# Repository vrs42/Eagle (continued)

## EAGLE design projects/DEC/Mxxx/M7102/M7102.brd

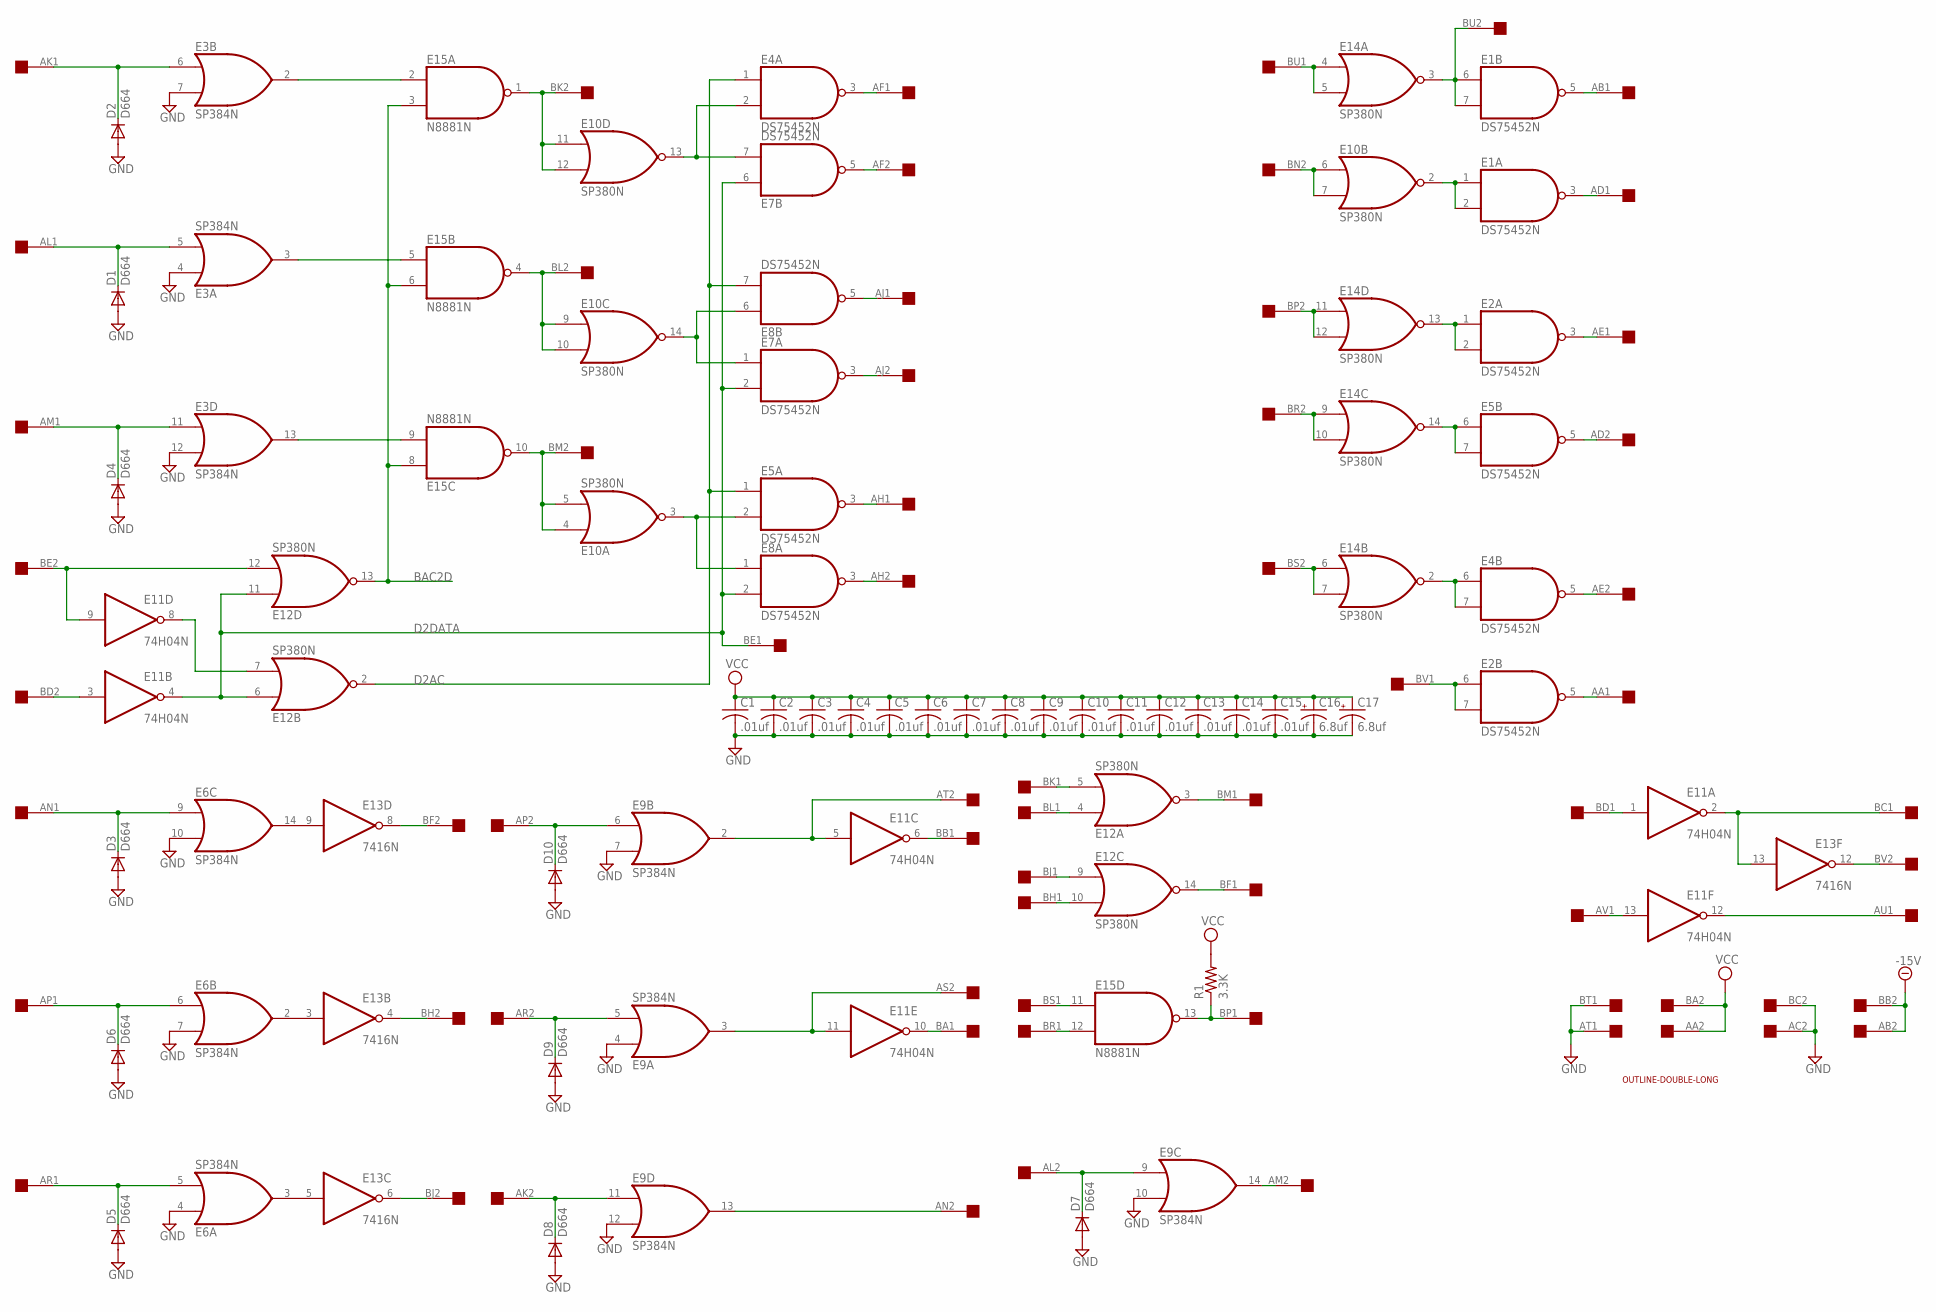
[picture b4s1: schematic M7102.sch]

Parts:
C1, C2, C3, C4, C5, C6, C7, C8, C9, C10, C11, C12, C13, C14, C15: .01uf; C050-025X075
C16, C17: 6.8uf; E15-5
D1, D2, D3, D4, D5, D6, D7, D8, D9, D10: D664; DO35-10
E1, E2, E4, E5, E7, E8: DS75452N; DIL08
E3, E6, E9: SP384N; DIL14
E10, E12, E14: SP380N; DIL14
E11: 74H04N; DIL14
E13: 7416N; DIL14
E15: N8881N; DIL14
EDGE: DOUBLE; EDGE-CON4
R1: 3.3K; 0207/10
U$3: OUTLINE-DOUBLE-LONG; DOUBLE-LONG

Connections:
-15V: EDGE.AB2, EDGE.BB2
AN1: D3.C, E6.9 (I0), EDGE.AN1
AP1: D6.C, E6.6 (I0), EDGE.AP1
AR1: D5.C, E6.5 (I1), EDGE.AR1
BAC2D: E12.13 (O), E15.3 (I1), E15.6 (I1), E15.8 (I0)
BD2: E11.3 (I), EDGE.BD2
BE2: E11.9 (I), E12.12 (I1), EDGE.BE2
D2AC: E4.1 (I0), E5.1 (I0), E8.7 (I1), E12.2 (O)
D2DATA: E7.2 (I1), E7.6 (I0), E8.2 (I1), E11.4 (O), E12.6 (I0), E12.11 (I0), EDGE.BE1
GND: C1.2, C2.2, C3.2, C4.2, C5.2, C6.2, C7.2, C8.2, C9.2, C10.2, C11.2, C12.2, C13.2, C14.2, C15.2, C16.-, C17.-, D1.A, D2.A, D3.A, D4.A, D5.A, D6.A, D7.A, D8.A, D9.A, D10.A, E1.4 (GND), E2.4 (GND), E3.1 (GND), E3.4 (I0), E3.7 (I1), E3.12 (I1), E4.4 (GND), E5.4 (GND), E6.1 (GND), E6.4 (I0), E6.7 (I1), E6.10 (I1), E7.4 (GND), E8.4 (GND), E9.1 (GND), E9.4 (I0), E9.7 (I1), E9.10 (I1), E9.12 (I1), E10.1 (GND), E11.7 (GND), E12.1 (GND), E13.7 (GND), E14.1 (GND), E15.7 (GND), EDGE.AC2, EDGE.AT1, EDGE.BC2, EDGE.BT1
unnamed: D4.C, E3.11 (I0), EDGE.AM1
unnamed: D1.C, E3.5 (I1), EDGE.AL1
unnamed: D2.C, E3.6 (I0), EDGE.AK1
unnamed: E3.2 (O), E15.2 (I0)
unnamed: E3.3 (O), E15.5 (I0)
unnamed: E3.13 (O), E15.9 (I1)
unnamed: E6.14 (O), E13.9 (I)
unnamed: E6.2 (O), E13.3 (I)
unnamed: E6.3 (O), E13.5 (I)
unnamed: E4.3 (O), EDGE.AF1
unnamed: E7.5 (O), EDGE.AF2
unnamed: E8.5 (O), EDGE.AJ1
unnamed: E11.8 (O), E12.7 (I1)
unnamed: D7.C, E9.9 (I0), EDGE.AL2
unnamed: E10.4 (I0), E10.5 (I1), E15.10 (O), EDGE.BM2
unnamed: E10.9 (I0), E10.10 (I1), E15.4 (O), EDGE.BL2
unnamed: E10.11 (I0), E10.12 (I1), E15.1 (O), EDGE.BK2
unnamed: E13.6 (O), EDGE.BJ2
unnamed: E13.4 (O), EDGE.BH2
unnamed: E13.8 (O), EDGE.BF2
unnamed: E4.2 (I1), E7.7 (I1), E10.13 (O)
unnamed: E7.1 (I0), E8.6 (I0), E10.14 (O)
unnamed: E5.2 (I1), E8.1 (I0), E10.3 (O)
unnamed: E9.14 (O), EDGE.AM2
unnamed: D10.C, E9.6 (I0), EDGE.AP2
unnamed: E5.3 (O), EDGE.AH1
unnamed: E7.3 (O), EDGE.AJ2
unnamed: E8.3 (O), EDGE.AH2
unnamed: E1.5 (O), EDGE.AB1
unnamed: E1.3 (O), EDGE.AD1
unnamed: E2.3 (O), EDGE.AE1
unnamed: E5.5 (O), EDGE.AD2
unnamed: E4.5 (O), EDGE.AE2
unnamed: E2.5 (O), EDGE.AA1
unnamed: D9.C, E9.5 (I1), EDGE.AR2
unnamed: D8.C, E9.11 (I0), EDGE.AK2
unnamed: E9.13 (O), EDGE.AN2
unnamed: E1.6 (I0), E1.7 (I1), E14.3 (O), EDGE.BU2
unnamed: E1.1 (I0), E1.2 (I1), E10.2 (O)
unnamed: E14.4 (I0), E14.5 (I1), EDGE.BU1
unnamed: E10.6 (I0), E10.7 (I1), EDGE.BN2
unnamed: E2.1 (I0), E2.2 (I1), E14.13 (O)
unnamed: E5.6 (I0), E5.7 (I1), E14.14 (O)
unnamed: E2.6 (I0), E2.7 (I1), EDGE.BV1
unnamed: E4.6 (I0), E4.7 (I1), E14.2 (O)
unnamed: E14.6 (I0), E14.7 (I1), EDGE.BS2
unnamed: E14.9 (I0), E14.10 (I1), EDGE.BR2
unnamed: E14.11 (I0), E14.12 (I1), EDGE.BP2
unnamed: E9.2 (O), E11.5 (I), EDGE.AT2
unnamed: E9.3 (O), E11.11 (I), EDGE.AS2
unnamed: E11.6 (O), EDGE.BB1
unnamed: E11.10 (O), EDGE.BA1
unnamed: E12.4 (I0), EDGE.BL1
unnamed: E12.5 (I1), EDGE.BK1
unnamed: E12.3 (O), EDGE.BM1
unnamed: E12.14 (O), EDGE.BF1
unnamed: E12.10 (I1), EDGE.BH1
unnamed: E12.9 (I0), EDGE.BJ1
unnamed: E15.11 (I0), EDGE.BS1
unnamed: E15.12 (I1), EDGE.BR1
unnamed: E15.13 (O), EDGE.BP1, R1.1
unnamed: E11.2 (O), E13.13 (I), EDGE.BC1
unnamed: E11.1 (I), EDGE.BD1
unnamed: E11.13 (I), EDGE.AV1
unnamed: E11.12 (O), EDGE.AU1
unnamed: E13.12 (O), EDGE.BV2
VCC: C1.1, C2.1, C3.1, C4.1, C5.1, C6.1, C7.1, C8.1, C9.1, C10.1, C11.1, C12.1, C13.1, C14.1, C15.1, C16.+, C17.+, E1.8 (VCC), E2.8 (VCC), E3.8 (VCC), E4.8 (VCC), E5.8 (VCC), E6.8 (VCC), E7.8 (VCC), E8.8 (VCC), E9.8 (VCC), E10.8 (VCC), E11.14 (VCC), E12.8 (VCC), E13.14 (VCC), E14.8 (VCC), E15.14 (VCC), EDGE.AA2, EDGE.BA2, R1.2

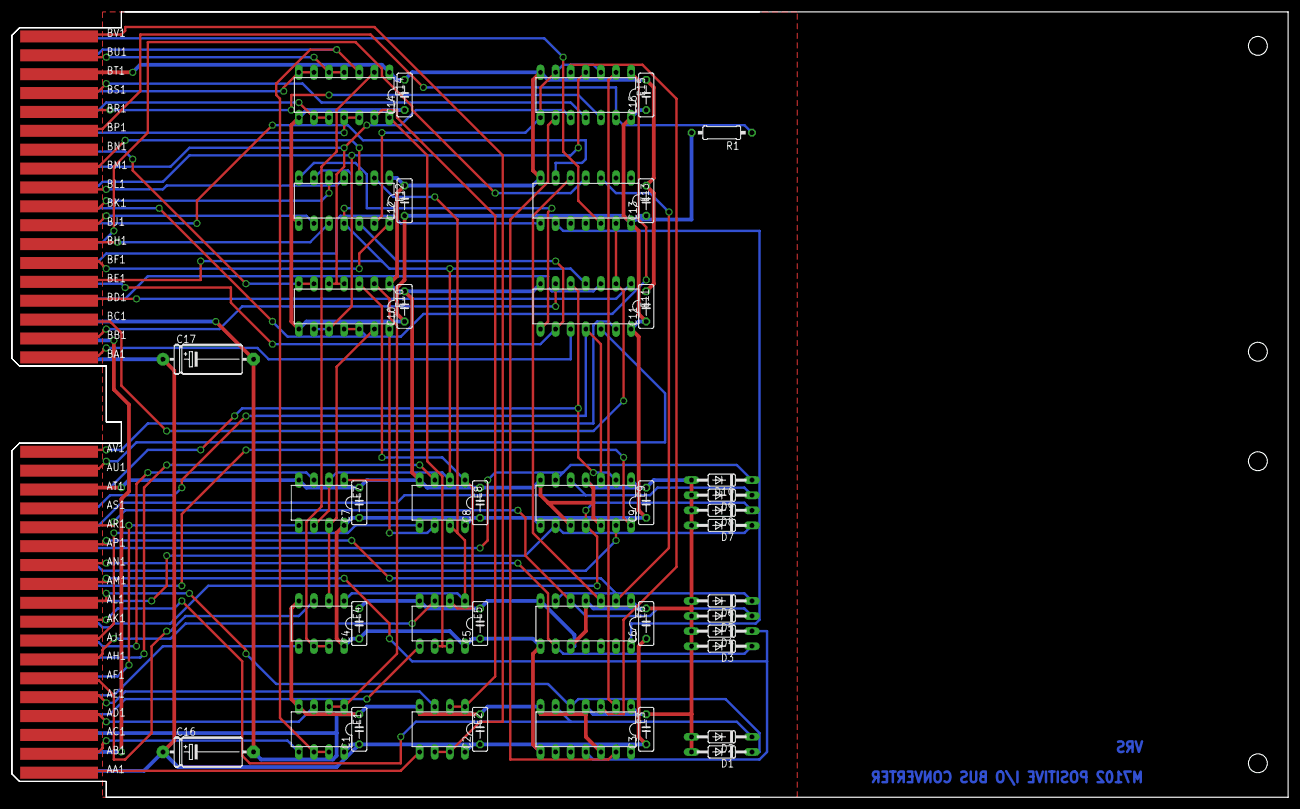
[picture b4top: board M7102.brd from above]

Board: 2 copper layers, 214.6 x 132.1 mm, 45 parts (0 on the bottom side), 77 nets.

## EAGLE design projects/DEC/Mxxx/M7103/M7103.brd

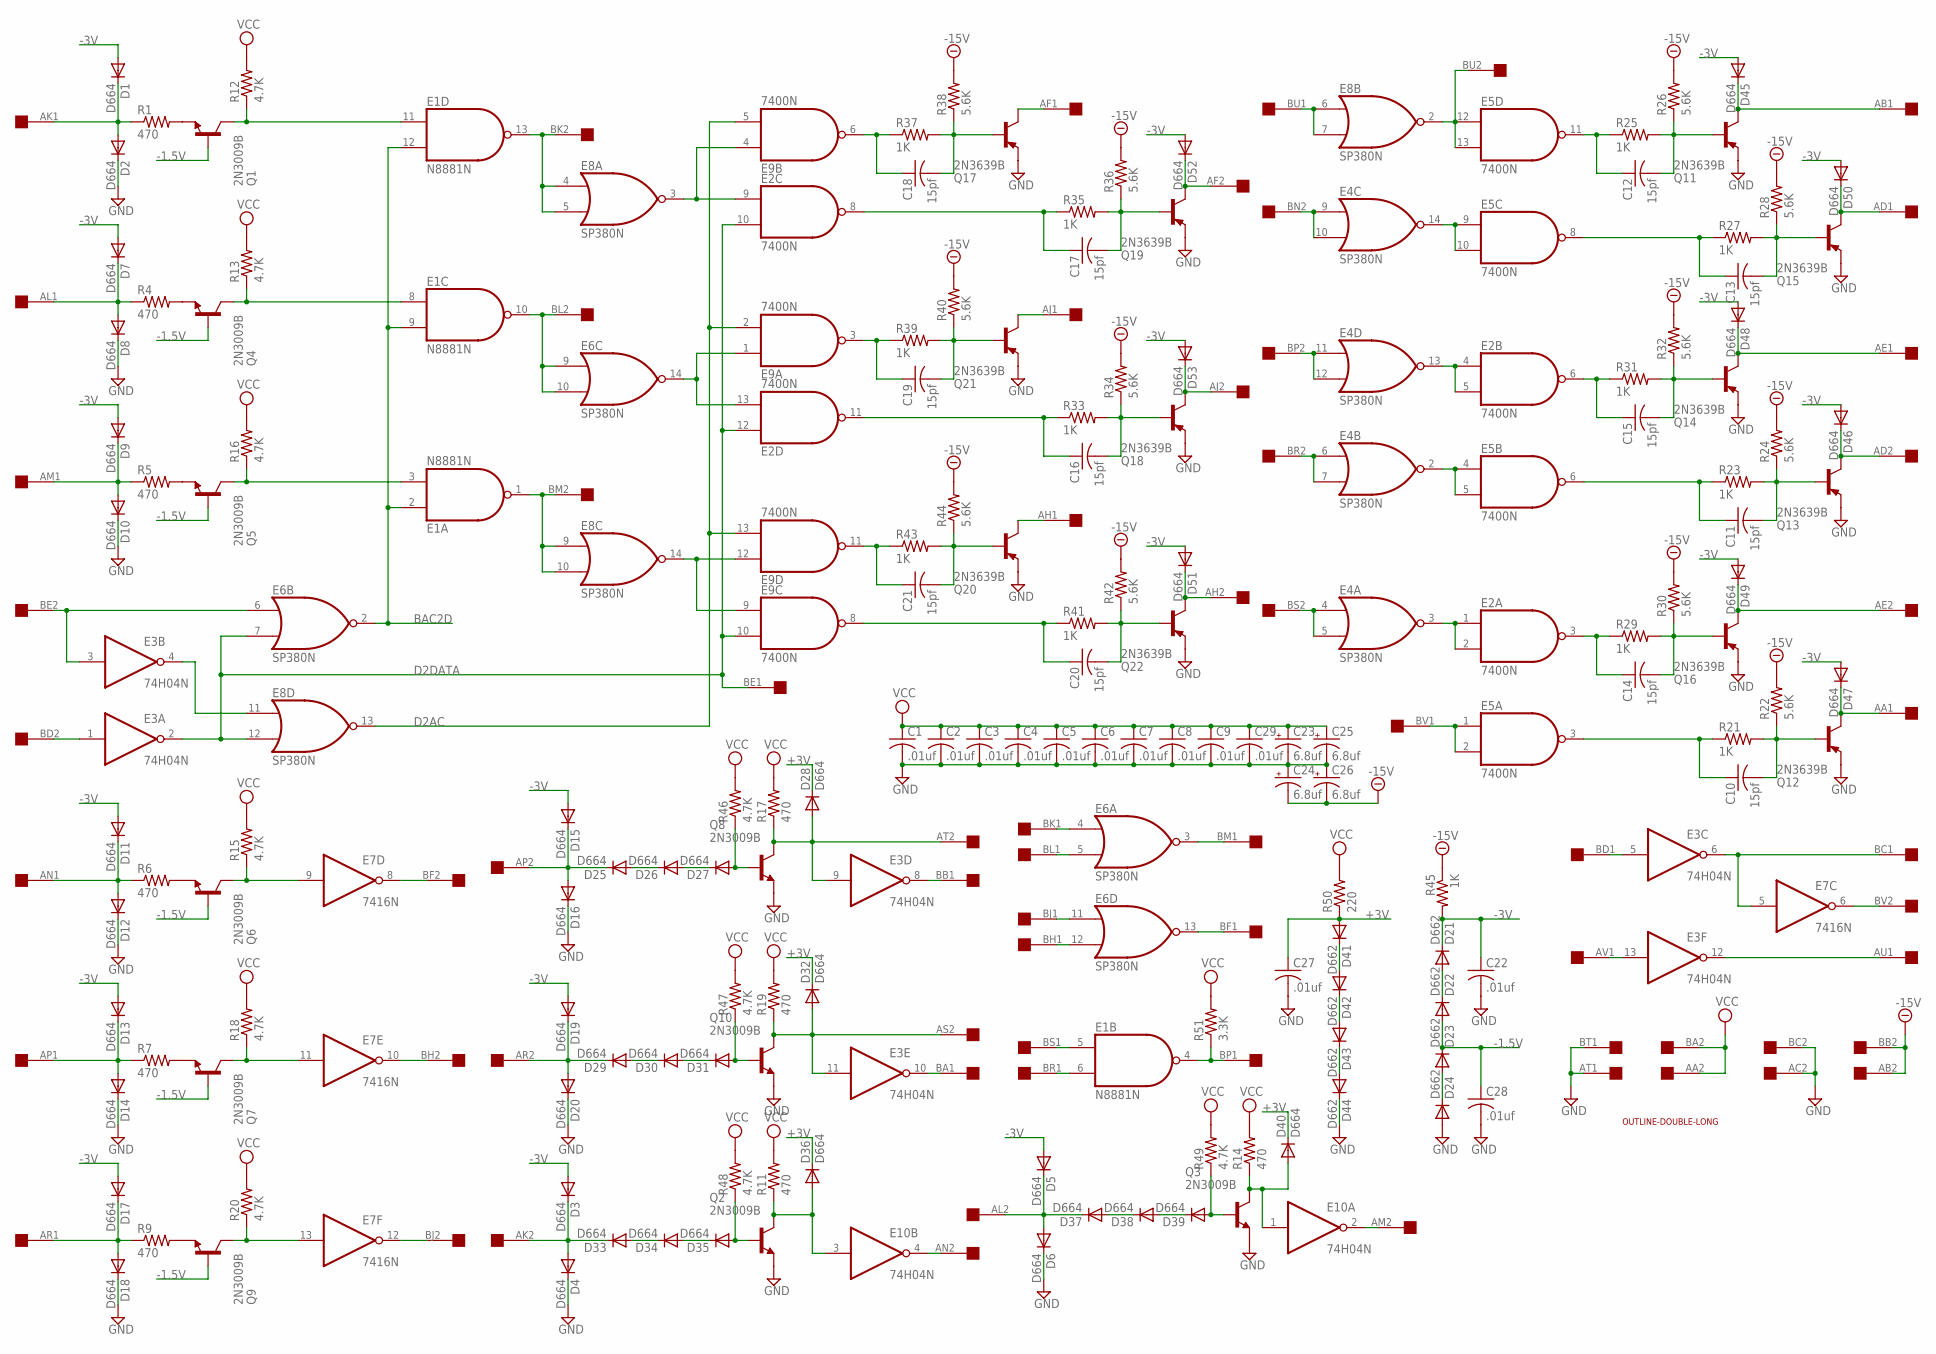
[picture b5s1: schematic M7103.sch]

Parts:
C1, C2, C3, C4, C5, C6, C7, C8, C9, C22, C27, C28, C29: .01uf; C050-025X075
C10, C11, C12, C13, C14, C15, C16, C17, C18, C19, C20, C21: 15pf; C050-025X075
C23, C24, C25, C26: 6.8uf; E15-5
D1, D2, D3, D4, D5, D6, D7, D8, D9, D10, D11, D12, D13, D14, D15, D16, D17, D18, D19, D20, D25, D26, D27, D28, D29, D30, D31, D32, D33, D34, D35, D36, D37, D38, D39, D40, D45, D46, D47, D48, D49, D50, D51, D52, D53: D664; DO35-10
D21, D22, D23, D24, D41, D42, D43, D44: D662; DO35-10
E1: N8881N; DIL14
E2, E5, E9: 7400N; DIL14
E3, E10: 74H04N; DIL14
E4, E6, E8: SP380N; DIL14
E7: 7416N; DIL14
EDGE: DOUBLE; EDGE-CON4
Q1, Q2, Q3, Q4, Q5, Q6, Q7, Q8, Q9, Q10: 2N3009B; TO39
Q11, Q12, Q13, Q14, Q15, Q16, Q17, Q18, Q19, Q20, Q21, Q22: 2N3639B; TO39
R1, R4, R5, R6, R7, R9, R11, R14, R17, R19: 470; 0207/10
R12, R13, R15, R16, R18, R20, R46, R47, R48, R49: 4.7K; 0207/10
R21, R23, R25, R27, R29, R31, R33, R35, R37, R39, R41, R43, R45: 1K; 0207/10
R22, R24, R26, R28, R30, R32, R34, R36, R38, R40, R42, R44: 5.6K; 0207/10
R50: 220; 0207/10
R51: 3.3K; 0207/10
U$3: OUTLINE-DOUBLE-LONG; DOUBLE-LONG

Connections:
+3V: C27.1, D28.C, D32.C, D36.C, D40.C, D41.A, R50.1
-1.5V: C28.1, D22.A, D23.C, Q1.2 (B), Q4.2 (B), Q5.2 (B), Q6.2 (B), Q7.2 (B), Q9.2 (B)
-3V: C22.1, D1.A, D3.A, D5.A, D7.A, D9.A, D11.A, D13.A, D15.A, D17.A, D19.A, D21.C, D45.A, D46.A, D47.A, D48.A, D49.A, D50.A, D51.A, D52.A, D53.A, R45.2
-15V: C24.-, C26.-, EDGE.AB2, EDGE.BB2, R22.2, R24.2, R26.2, R28.2, R30.2, R32.2, R34.2, R36.2, R38.2, R40.2, R42.2, R44.2, R45.1
AK1: D1.C, D2.A, EDGE.AK1, R1.1
AL1: D7.C, D8.A, EDGE.AL1, R4.1
AM1: D9.C, D10.A, EDGE.AM1, R5.1
AN1: D11.C, D12.A, EDGE.AN1, R6.1
AP1: D13.C, D14.A, EDGE.AP1, R7.1
AR1: D17.C, D18.A, EDGE.AR1, R9.1
BAC2D: E1.2 (I0), E1.9 (I1), E1.12 (I1), E6.2 (O)
BD2: E3.1 (I), EDGE.BD2
BE2: E3.3 (I), E6.6 (I0), EDGE.BE2
D2AC: E8.13 (O), E9.2 (I1), E9.5 (I1), E9.13 (I1)
D2DATA: E2.10 (I1), E2.12 (I0), E3.2 (O), E6.7 (I1), E8.12 (I1), E9.10 (I1), EDGE.BE1
GND: C1.2, C2.2, C3.2, C4.2, C5.2, C6.2, C7.2, C8.2, C9.2, C22.2, C23.-, C24.+, C25.-, C26.+, C27.2, C28.2, C29.2, D2.C, D4.C, D6.C, D8.C, D10.C, D12.C, D14.C, D16.C, D18.C, D20.C, D24.A, D44.C, E1.7 (GND), E2.7 (GND), E3.7 (GND), E4.1 (GND), E5.7 (GND), E6.1 (GND), E7.7 (GND), E8.1 (GND), E9.7 (GND), E10.7 (GND), EDGE.AC2, EDGE.AT1, EDGE.BC2, EDGE.BT1, Q2.1 (E), Q3.1 (E), Q8.1 (E), Q10.1 (E), Q11.1 (E), Q12.1 (E), Q13.1 (E), Q14.1 (E), Q15.1 (E), Q16.1 (E), Q17.1 (E), Q18.1 (E), Q19.1 (E), Q20.1 (E), Q21.1 (E), Q22.1 (E)
unnamed: Q4.1 (E), R4.2
unnamed: E1.8 (I0), Q4.3 (C), R13.1
unnamed: Q1.1 (E), R1.2
unnamed: Q5.1 (E), R5.2
unnamed: E1.11 (I0), Q1.3 (C), R12.1
unnamed: E1.3 (I1), Q5.3 (C), R16.1
unnamed: Q6.1 (E), R6.2
unnamed: E7.9 (I), Q6.3 (C), R15.1
unnamed: Q7.1 (E), R7.2
unnamed: E7.11 (I), Q7.3 (C), R18.1
unnamed: Q9.1 (E), R9.2
unnamed: E7.13 (I), Q9.3 (C), R20.1
unnamed: E3.4 (O), E8.11 (I0)
unnamed: D15.C, D16.A, D25.C, EDGE.AP2
unnamed: E1.1 (O), E8.9 (I0), E8.10 (I1), EDGE.BM2
unnamed: E1.10 (O), E6.9 (I0), E6.10 (I1), EDGE.BL2
unnamed: E1.13 (O), E8.4 (I0), E8.5 (I1), EDGE.BK2
unnamed: E7.12 (O), EDGE.BJ2
unnamed: E7.10 (O), EDGE.BH2
unnamed: E7.8 (O), EDGE.BF2
unnamed: E2.9 (I0), E8.3 (O), E9.4 (I0)
unnamed: E2.13 (I1), E6.14 (O), E9.1 (I0)
unnamed: E8.14 (O), E9.9 (I0), E9.12 (I0)
unnamed: D27.A, Q8.2 (B), R46.1
unnamed: D25.A, D26.C
unnamed: C18.1, E9.6 (O), R37.1
unnamed: C18.2, Q17.2 (B), R37.2, R38.1
unnamed: EDGE.AF1, Q17.3 (C)
unnamed: C17.1, E2.8 (O), R35.1
unnamed: C17.2, Q19.2 (B), R35.2, R36.1
unnamed: D52.C, EDGE.AF2, Q19.3 (C)
unnamed: C12.1, E5.11 (O), R25.1
unnamed: C12.2, Q11.2 (B), R25.2, R26.1
unnamed: D45.C, EDGE.AB1, Q11.3 (C)
unnamed: C13.1, E5.8 (O), R27.1
unnamed: C13.2, Q15.2 (B), R27.2, R28.1
unnamed: D50.C, EDGE.AD1, Q15.3 (C)
unnamed: E5.12 (I0), E5.13 (I1), E8.2 (O), EDGE.BU2
unnamed: E4.14 (O), E5.9 (I0), E5.10 (I1)
unnamed: E8.6 (I0), E8.7 (I1), EDGE.BU1
unnamed: E4.9 (I0), E4.10 (I1), EDGE.BN2
unnamed: C19.1, E9.3 (O), R39.1
unnamed: C19.2, Q21.2 (B), R39.2, R40.1
unnamed: EDGE.AJ1, Q21.3 (C)
unnamed: C16.1, E2.11 (O), R33.1
unnamed: C16.2, Q18.2 (B), R33.2, R34.1
unnamed: D53.C, EDGE.AJ2, Q18.3 (C)
unnamed: C21.1, E9.11 (O), R43.1
unnamed: C21.2, Q20.2 (B), R43.2, R44.1
unnamed: EDGE.AH1, Q20.3 (C)
unnamed: C20.1, E9.8 (O), R41.1
unnamed: C20.2, Q22.2 (B), R41.2, R42.1
unnamed: D51.C, EDGE.AH2, Q22.3 (C)
unnamed: C15.1, E2.6 (O), R31.1
unnamed: C15.2, Q14.2 (B), R31.2, R32.1
unnamed: D48.C, EDGE.AE1, Q14.3 (C)
unnamed: C11.1, E5.6 (O), R23.1
unnamed: C11.2, Q13.2 (B), R23.2, R24.1
unnamed: D46.C, EDGE.AD2, Q13.3 (C)
unnamed: C14.1, E2.3 (O), R29.1
unnamed: C14.2, Q16.2 (B), R29.2, R30.1
unnamed: D49.C, EDGE.AE2, Q16.3 (C)
unnamed: C10.1, E5.3 (O), R21.1
unnamed: C10.2, Q12.2 (B), R21.2, R22.1
unnamed: D47.C, EDGE.AA1, Q12.3 (C)
unnamed: E2.4 (I0), E2.5 (I1), E4.13 (O)
unnamed: E4.2 (O), E5.4 (I0), E5.5 (I1)
unnamed: E5.1 (I0), E5.2 (I1), EDGE.BV1
unnamed: E2.1 (I0), E2.2 (I1), E4.3 (O)
unnamed: E4.4 (I0), E4.5 (I1), EDGE.BS2
unnamed: E4.6 (I0), E4.7 (I1), EDGE.BR2
unnamed: E4.11 (I0), E4.12 (I1), EDGE.BP2
unnamed: D26.A, D27.C
unnamed: D28.A, E3.9 (I), EDGE.AT2, Q8.3 (C), R17.1
unnamed: D31.A, Q10.2 (B), R47.1
unnamed: D29.A, D30.C
unnamed: D30.A, D31.C
unnamed: D32.A, E3.11 (I), EDGE.AS2, Q10.3 (C), R19.1
unnamed: D35.A, Q2.2 (B), R48.1
unnamed: D33.A, D34.C
unnamed: D34.A, D35.C
unnamed: D36.A, E10.3 (I), Q2.3 (C), R11.1
unnamed: D39.A, Q3.2 (B), R49.1
unnamed: D37.A, D38.C
unnamed: D38.A, D39.C
unnamed: D40.A, E10.1 (I), Q3.3 (C), R14.1
unnamed: E10.4 (O), EDGE.AN2
unnamed: E3.8 (O), EDGE.BB1
unnamed: E3.10 (O), EDGE.BA1
unnamed: E10.2 (O), EDGE.AM2
unnamed: E6.5 (I1), EDGE.BL1
unnamed: E6.4 (I0), EDGE.BK1
unnamed: E6.3 (O), EDGE.BM1
unnamed: E6.13 (O), EDGE.BF1
unnamed: E6.12 (I1), EDGE.BH1
unnamed: E6.11 (I0), EDGE.BJ1
unnamed: E1.5 (I0), EDGE.BS1
unnamed: E1.6 (I1), EDGE.BR1
unnamed: E1.4 (O), EDGE.BP1, R51.1
unnamed: E3.6 (O), E7.5 (I), EDGE.BC1
unnamed: E3.5 (I), EDGE.BD1
unnamed: E3.13 (I), EDGE.AV1
unnamed: E3.12 (O), EDGE.AU1
unnamed: E7.6 (O), EDGE.BV2
unnamed: D23.A, D24.C
unnamed: D3.C, D4.A, D33.C, EDGE.AK2
unnamed: D41.C, D42.A
unnamed: D42.C, D43.A
unnamed: D43.C, D44.A
unnamed: D21.A, D22.C
unnamed: D19.C, D20.A, D29.C, EDGE.AR2
unnamed: D5.C, D6.A, D37.C, EDGE.AL2
VCC: C1.1, C2.1, C3.1, C4.1, C5.1, C6.1, C7.1, C8.1, C9.1, C23.+, C25.+, C29.1, E1.14 (VCC), E2.14 (VCC), E3.14 (VCC), E4.8 (VCC), E5.14 (VCC), E6.8 (VCC), E7.14 (VCC), E8.8 (VCC), E9.14 (VCC), E10.14 (VCC), EDGE.AA2, EDGE.BA2, R11.2, R12.2, R13.2, R14.2, R15.2, R16.2, R17.2, R18.2, R19.2, R20.2, R46.2, R47.2, R48.2, R49.2, R50.2, R51.2

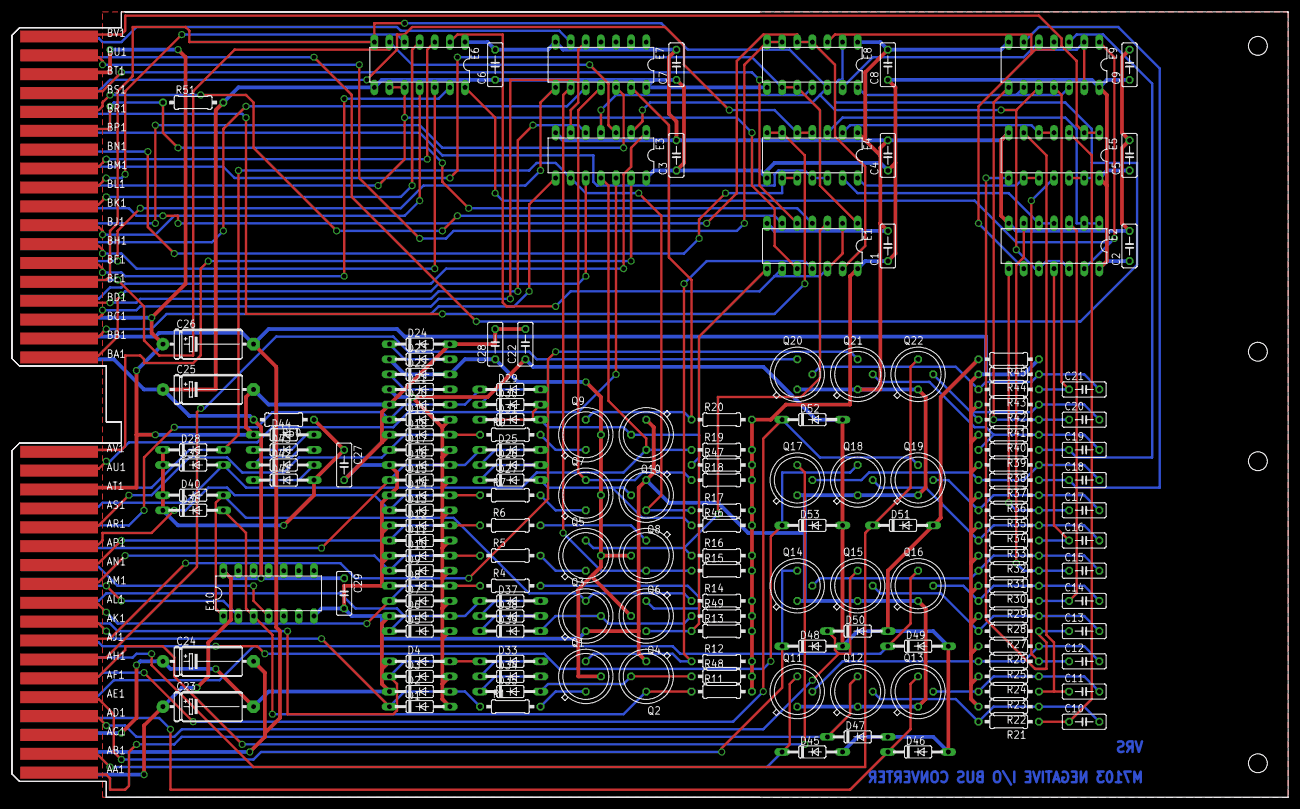
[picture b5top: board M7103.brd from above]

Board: 2 copper layers, 214.6 x 132.1 mm, 163 parts (0 on the bottom side), 129 nets.
